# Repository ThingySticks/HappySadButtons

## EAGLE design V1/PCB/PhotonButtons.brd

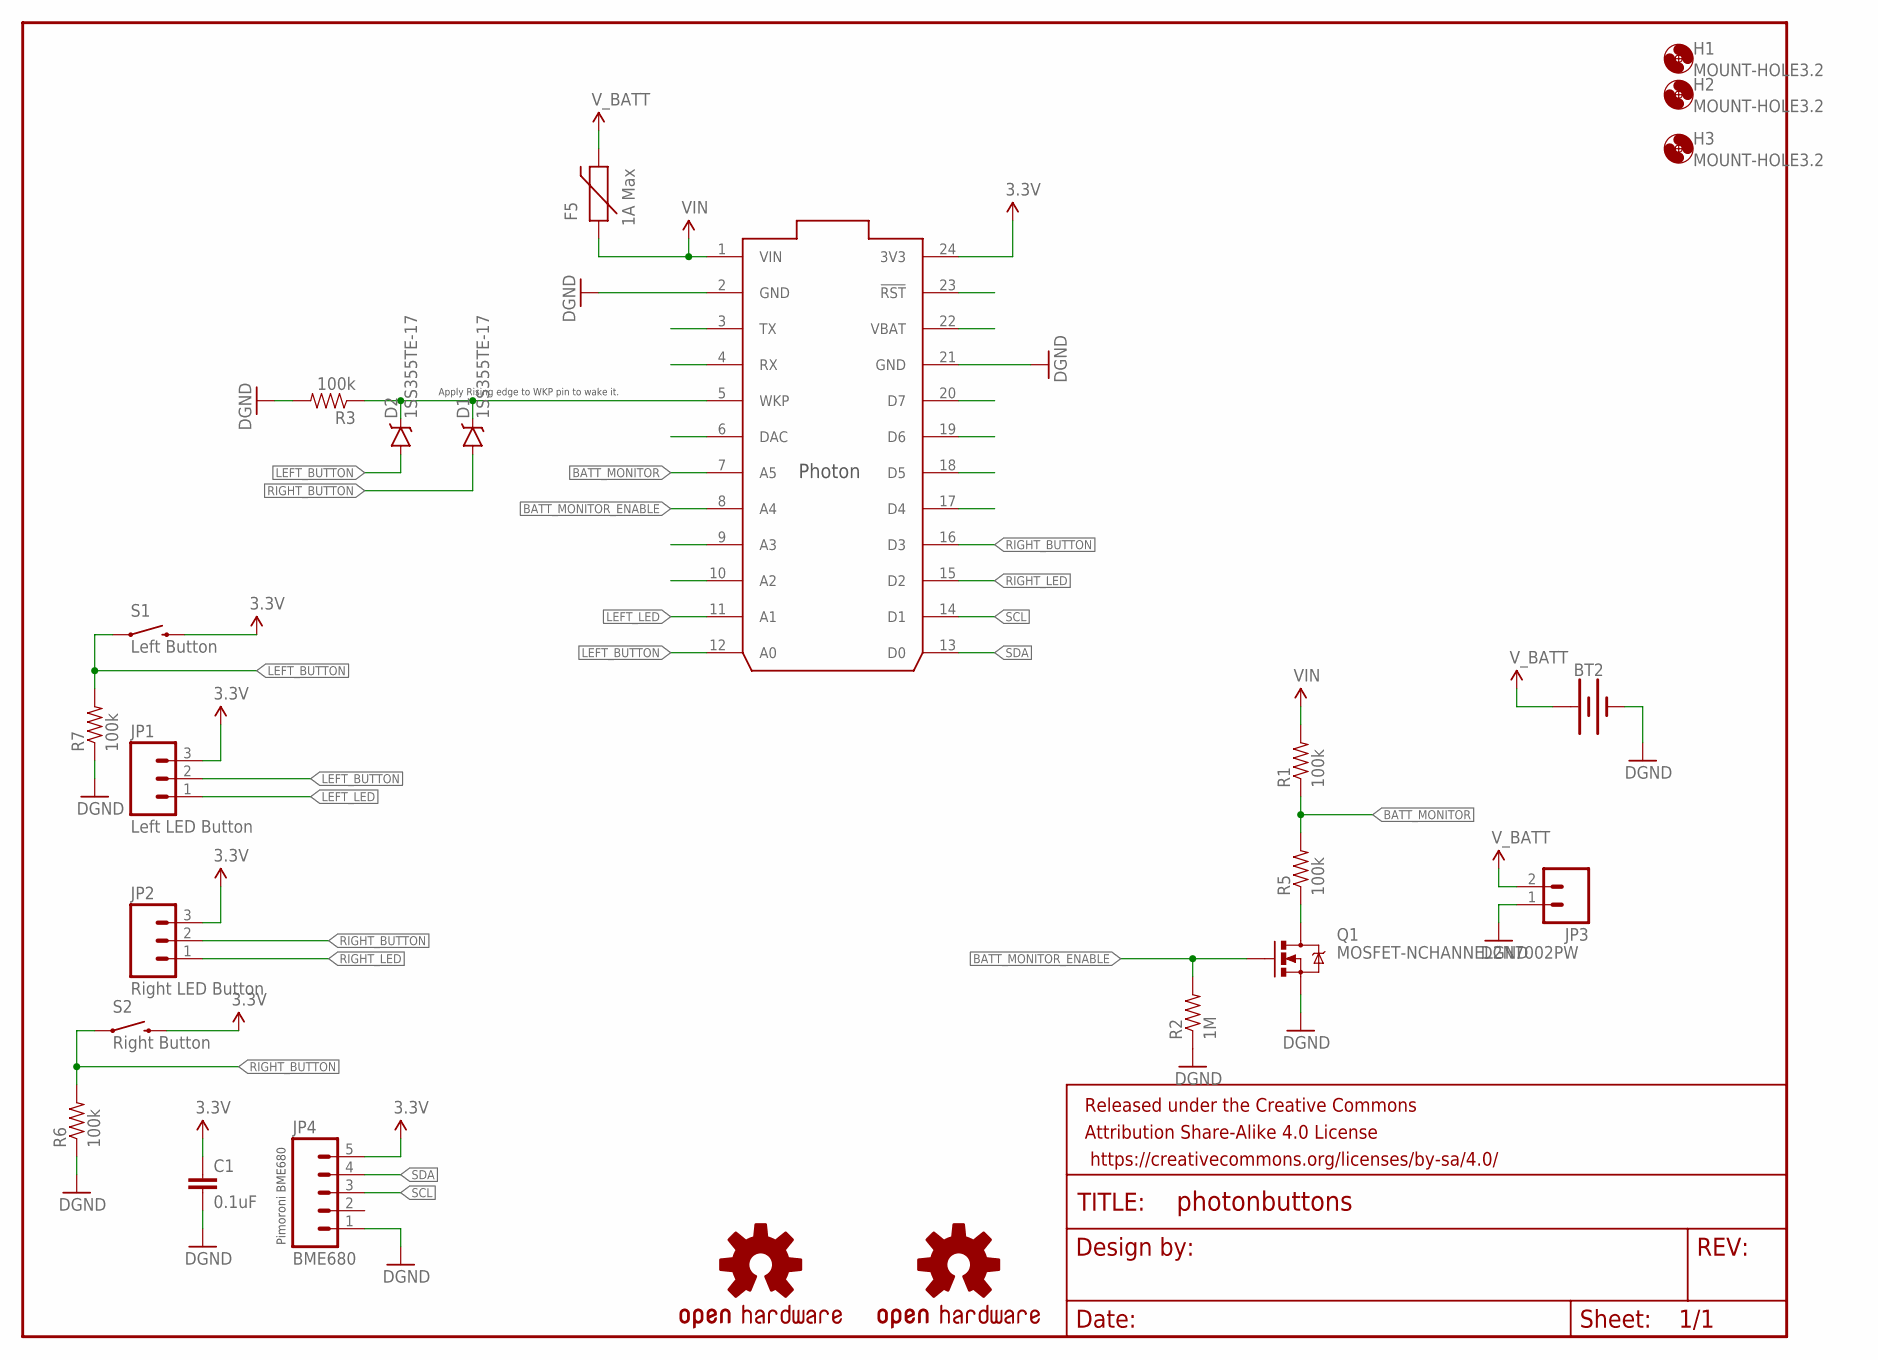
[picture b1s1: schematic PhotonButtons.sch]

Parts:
BT2: BATTERY-16340; BATTERY_16340-HOLDER
C1: 0.1uF; 0805
D1, D2: 1SS355TE-17; SOD-323; FARNELL 152-5435
F5: 1A Max; PTC-1206
FRAME1: FRAME-LETTER; CREATIVE_COMMONS
H1, H2, H3: MOUNT-HOLE3.2; 3,2
JP1: Left LED Button; MOLEX-1X3
JP2: Right LED Button; MOLEX-1X3
JP3: M02-JST-2MM-SMT; JST-2-SMD
JP4: BME680; 1X05
LOGO1, LOGO2: OSHW-LOGOL; OSHW-LOGO-L
Q1: MOSFET-NCHANNEL2N7002PW; SOT323; FARNELL 189-4713
R1, R3, R5, R6, R7: 100k; 0805
R2: 1M; 0805
S1: Left Button; TACTILE-PTH
S2: Right Button; TACTILE-PTH
U$1: PHOTON_SMD

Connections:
3.3V: C1.1, JP1.3, JP2.3, JP4.5, S1.3 (2), S2.3 (2), U$1.24 (3V3)
BATT_MONITOR: R1.1, R5.2, U$1.7 (A5)
BATT_MONITOR_ENABLE: Q1.1 (G), R2.2, U$1.8 (A4)
GND: BT2.P$2 (-), C1.2, JP3.1 (2), JP4.1, Q1.2 (S), R2.1, R3.2, R6.1, R7.1, U$1.2 (GND), U$1.21 (GND)
LEFT_BUTTON: D2.A, JP1.2, R7.2, S1.1, U$1.12 (A0)
LEFT_LED: JP1.1, U$1.11 (A1)
unnamed: Q1.3 (D), R5.1
unnamed: D1.C, D2.C, R3.1, U$1.5 (WKP)
RIGHT_BUTTON: D1.A, JP2.2, R6.2, S2.1, U$1.16 (D3)
RIGHT_LED: JP2.1, U$1.15 (D2)
SCL: JP4.3, U$1.14 (D1)
SDA: JP4.4, U$1.13 (D0)
VIN: F5.1, R1.2, U$1.1 (VIN)
V_BATT: BT2.P$1 (+), F5.2, JP3.2 (1)

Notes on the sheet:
Apply Rising edge to WKP pin to wake it.
Pimoroni BME680

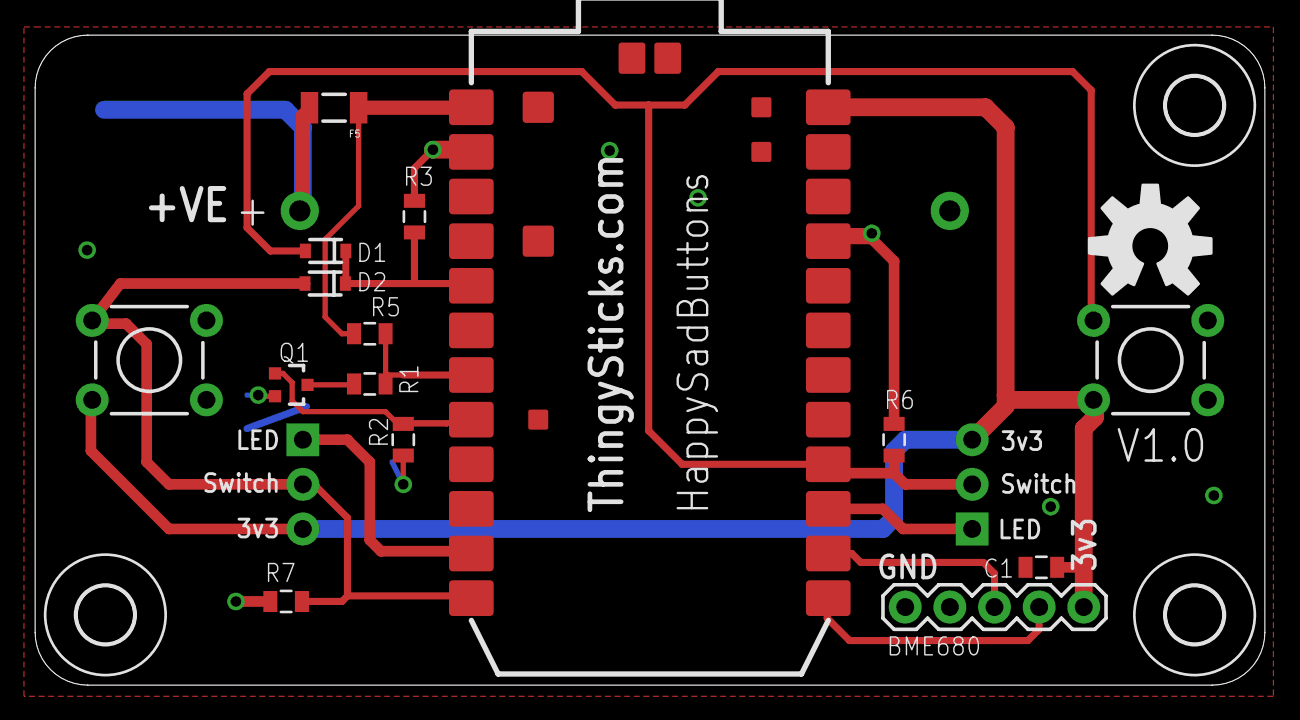
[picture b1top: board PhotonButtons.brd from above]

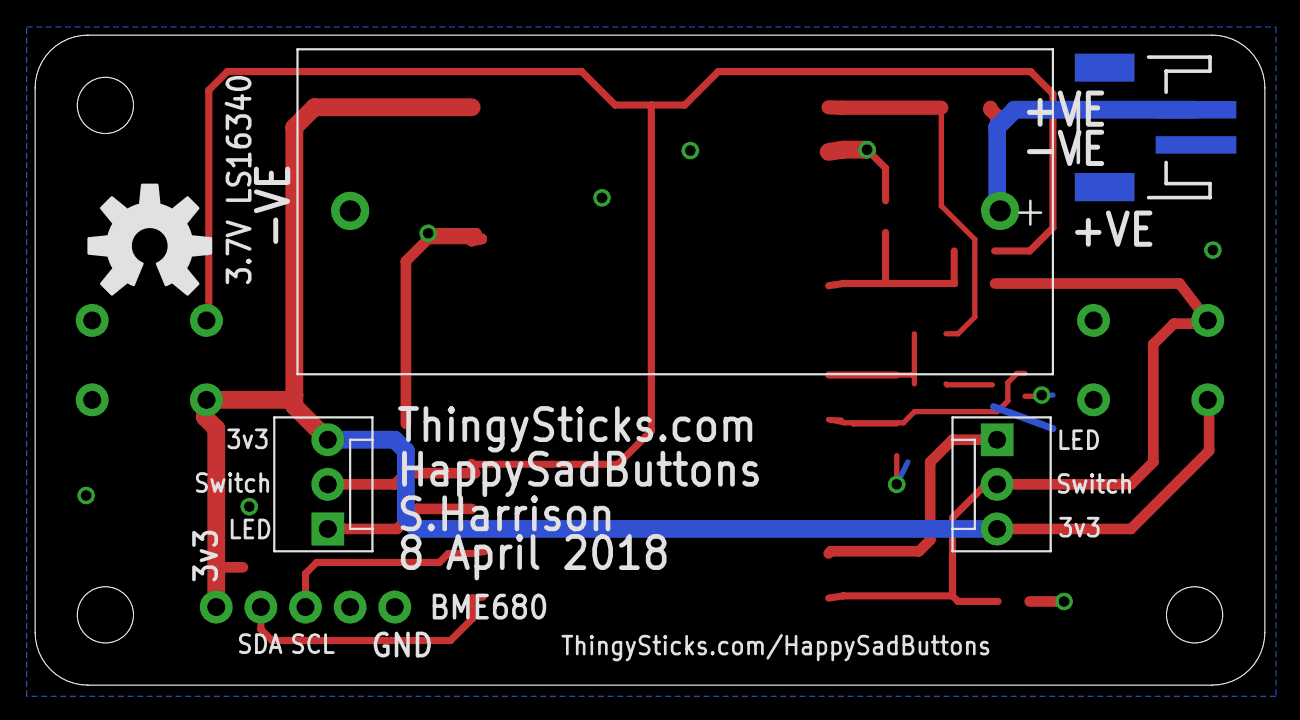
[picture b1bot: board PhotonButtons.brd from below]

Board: 2 copper layers, 70.0 x 37.0 mm, 25 parts (5 on the bottom side), 14 nets.

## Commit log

2018-04-08 Initial version
2018-05-13 Added enclosure
2018-05-13 Labels for the case.
2018-05-13 PCB images.
2018-05-13 Added components values

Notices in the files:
parts and their libraries:
SparkFun-DiscreteSemi: Licensing: Creative Commons ShareAlike 4.0 International - https://creativecommons.org/licenses/by-sa/4.0
SparkFun-Aesthetics: Released under the Creative Commons Attribution Share-Alike 4.0 License
SparkFun-Aesthetics: https://creativecommons.org/licenses/by-sa/4.0
